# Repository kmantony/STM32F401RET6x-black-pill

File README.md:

Schematic,  PCB layout, PDF export of schematic, PCB layout/render images, BOM with estimated component cost, Short design description, ERC and DRC "Results"  are all in the result folder.

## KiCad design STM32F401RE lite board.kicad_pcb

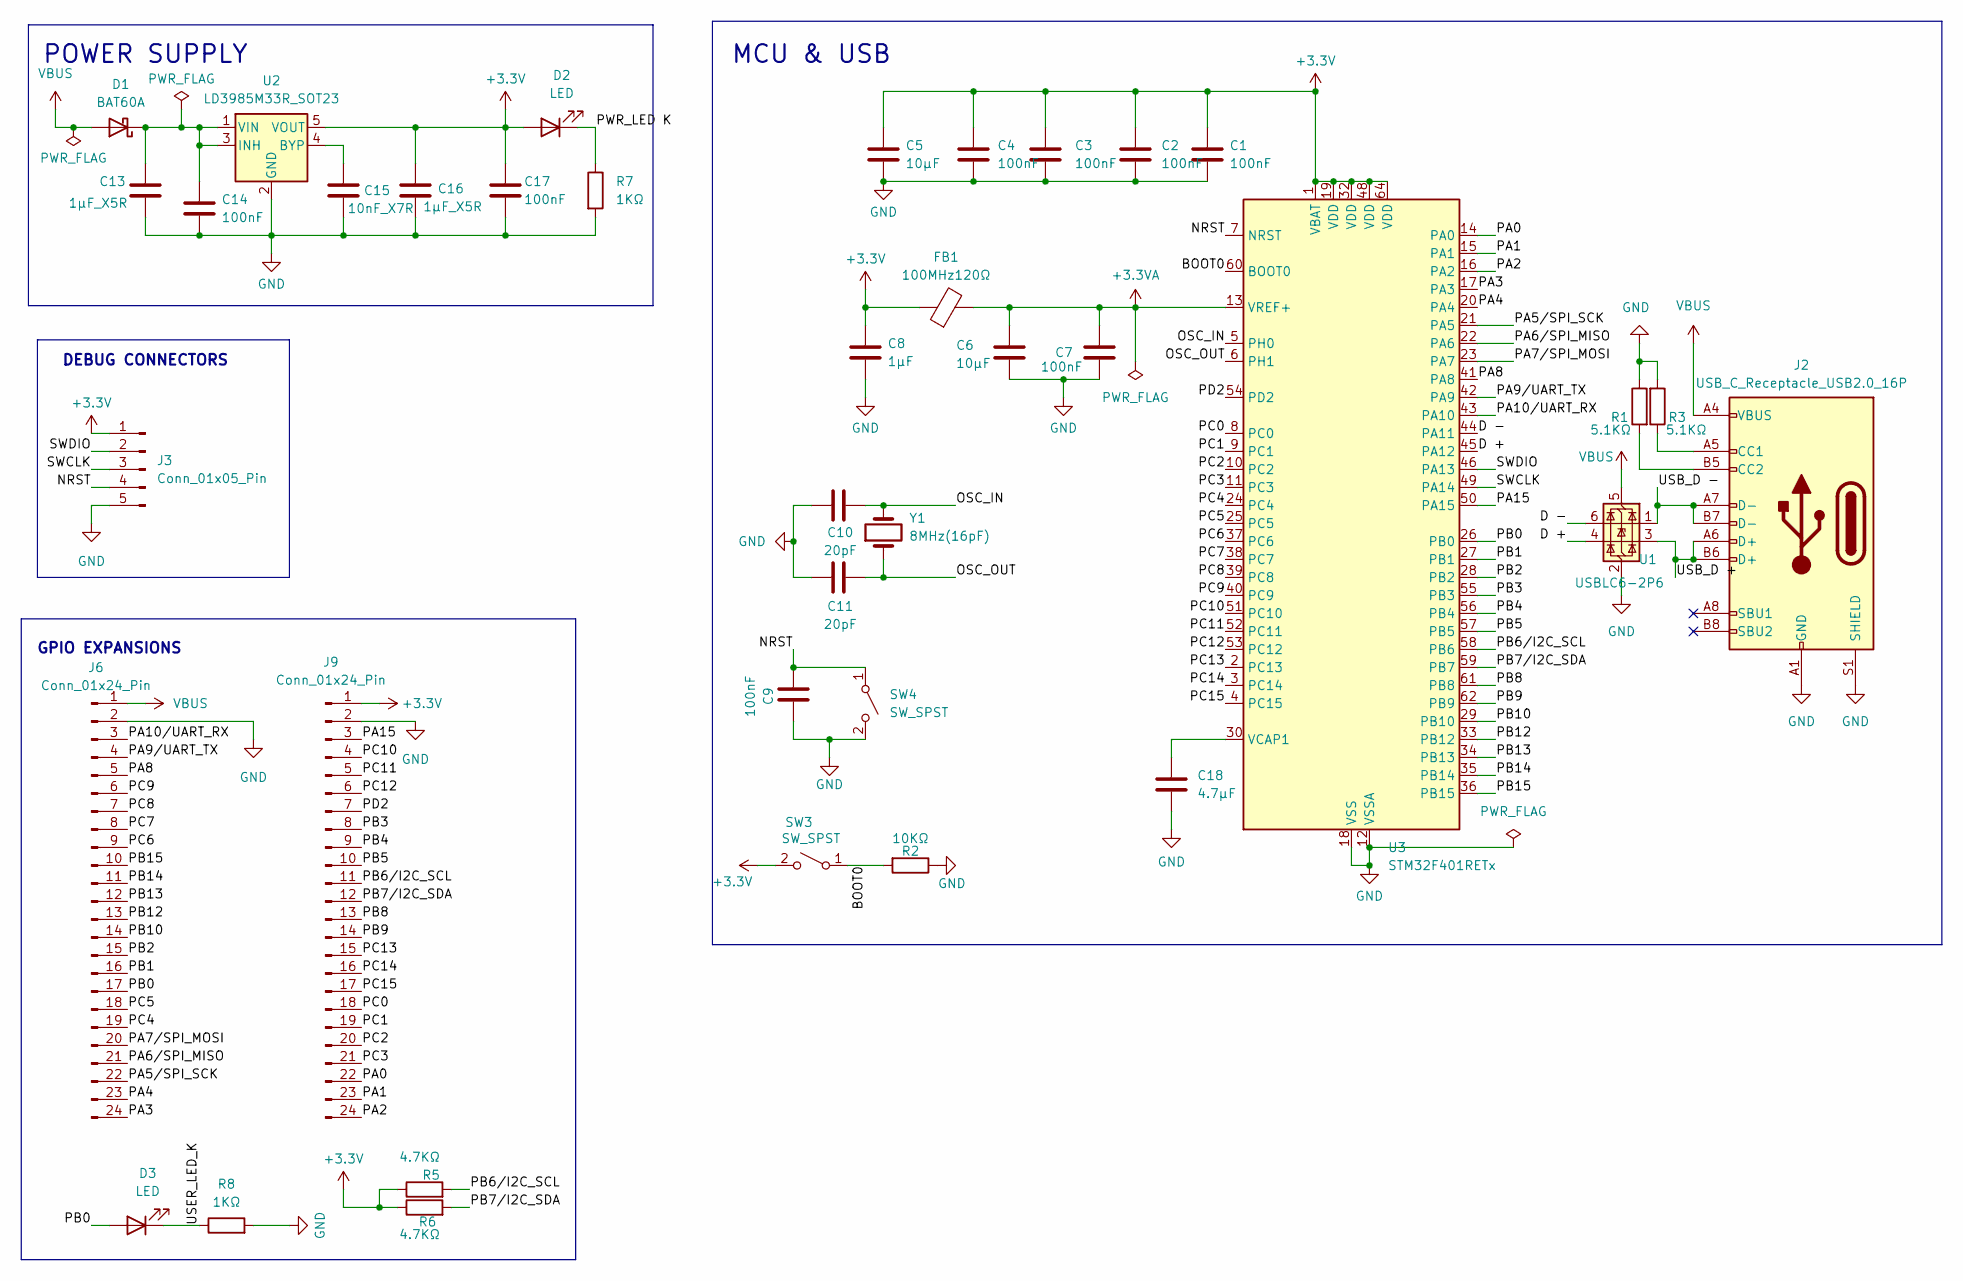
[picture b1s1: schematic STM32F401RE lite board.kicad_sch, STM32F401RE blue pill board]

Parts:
C1, C2, C3, C4, C7, C17: 100nF; C_0402_1005Metric
C5, C6: 10µF; C_0805_2012Metric
C8: 1µF; C_0402_1005Metric
C9, C14: 100nF; C_0603_1608Metric
C10, C11: 20pF; C_0402_1005Metric
C13, C16: 1µF_X5R; C_0402_1005Metric
C15: 10nF_X7R; C_0402_1005Metric
C18: 4.7µF; C_0805_2012Metric
D1: BAT60A; D_SOD-323
D2, D3: LED; LED_0603_1608Metric
FB1: 100MHz120Ω; L_0603_1608Metric
J2: USB_C_Receptacle_USB2.0_16P; USB_C_Receptacle_HRO_TYPE-C-31-M-12
J3: Conn_01x05_Pin; PinHeader_1x05_P2.54mm_Vertical
J6, J9: Conn_01x24_Pin; PinHeader_1x24_P2.54mm_Vertical
R1, R3: 5.1KΩ; R_0402_1005Metric
R2: 10KΩ; R_0402_1005Metric
R5, R6: 4.7KΩ; R_0402_1005Metric
R7, R8: 1KΩ; R_0402_1005Metric
SW3, SW4: SW_SPST; SW_SPST_TL3342
U1: USBLC6-2P6; SOT-666
U2: LD3985M33R_SOT23; SOT-23-5
U3: STM32F401RETx; LQFP-64_10x10mm_P0.5mm
Y1: 8MHz(16pF); Crystal_HC49-4H_Vertical

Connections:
+3.3V: C1.1, C2.1, C3.1, C4.1, C5.1, C8.1, C16.1, C17.1, D2.2 (A), FB1.1, J3.1, J9.1, R5.1, R6.1, SW3.2 (B), U2.5 (VOUT), U3.1 (VBAT), U3.19 (VDD), U3.32 (VDD), U3.48 (VDD), U3.64 (VDD)
+3.3VA: C6.1, C7.1, FB1.2, U3.13 (VREF+)
/BOOT0: R2.2, SW3.1 (A), U3.60 (BOOT0)
/D +: U1.4 (I/O2), U3.45 (PA12)
/D -: U1.6 (I/O1), U3.44 (PA11)
/NRST: C9.2, J3.4, SW4.1 (A), U3.7 (NRST)
/OSC_IN: C10.2, U3.5 (PH0), Y1.2
/OSC_OUT: C11.2, U3.6 (PH1), Y1.1
/PA0: J9.22, U3.14 (PA0)
/PA1: J9.23, U3.15 (PA1)
/PA2: J9.24, U3.16 (PA2)
/PA3: J6.24, U3.17 (PA3)
/PA4: J6.23, U3.20 (PA4)
/PA5/SPI_SCK: J6.22, U3.21 (PA5)
/PA6/SPI_MISO: J6.21, U3.22 (PA6)
/PA7/SPI_MOSI: J6.20, U3.23 (PA7)
/PA8: J6.5, U3.41 (PA8)
/PA9/UART_TX: J6.4, U3.42 (PA9)
/PA10/UART_RX: J6.3, U3.43 (PA10)
/PA15: J9.3, U3.50 (PA15)
/PB0: D3.2 (A), J6.17, U3.26 (PB0)
/PB1: J6.16, U3.27 (PB1)
/PB2: J6.15, U3.28 (PB2)
/PB3: J9.8, U3.55 (PB3)
/PB4: J9.9, U3.56 (PB4)
/PB5: J9.10, U3.57 (PB5)
/PB6/I2C_SCL: J9.11, R5.2, U3.58 (PB6)
/PB7/I2C_SDA: J9.12, R6.2, U3.59 (PB7)
/PB8: J9.13, U3.61 (PB8)
/PB9: J9.14, U3.62 (PB9)
/PB10: J6.14, U3.29 (PB10)
/PB12: J6.13, U3.33 (PB12)
/PB13: J6.12, U3.34 (PB13)
/PB14: J6.11, U3.35 (PB14)
/PB15: J6.10, U3.36 (PB15)
/PC0: J9.18, U3.8 (PC0)
/PC1: J9.19, U3.9 (PC1)
/PC2: J9.20, U3.10 (PC2)
/PC3: J9.21, U3.11 (PC3)
/PC4: J6.19, U3.24 (PC4)
/PC5: J6.18, U3.25 (PC5)
/PC6: J6.9, U3.37 (PC6)
/PC7: J6.8, U3.38 (PC7)
/PC8: J6.7, U3.39 (PC8)
/PC9: J6.6, U3.40 (PC9)
/PC10: J9.4, U3.51 (PC10)
/PC11: J9.5, U3.52 (PC11)
/PC12: J9.6, U3.53 (PC12)
/PC13: J9.15, U3.2 (PC13)
/PC14: J9.16, U3.3 (PC14)
/PC15: J9.17, U3.4 (PC15)
/PD2: J9.7, U3.54 (PD2)
/PWR_LED K: D2.1 (K), R7.1
/SWCLK: J3.3, U3.49 (PA14)
/SWDIO: J3.2, U3.46 (PA13)
/USB_D +: J2.A6 (D+), J2.B6 (D+), U1.3 (I/O2)
/USB_D -: J2.A7 (D-), J2.B7 (D-), U1.1 (I/O1)
/USER_LED_K: D3.1 (K), R8.1
GND: C1.2, C2.2, C3.2, C4.2, C5.2, C6.2, C7.2, C8.2, C9.1, C10.1, C11.1, C13.2, C14.2, C15.2, C16.2, C17.2, C18.2, J2.A1 (GND), J2.A12 (GND), J2.B1 (GND), J2.B12 (GND), J2.S1 (SHIELD), J3.5, J6.2, J9.2, R1.1, R2.1, R3.2, R7.2, R8.2, SW4.2 (B), U1.2 (GND), U2.2 (GND), U3.12 (VSSA), U3.18 (VSS), U3.31 (VSS), U3.47 (VSS), U3.63 (VSS)
unnamed: C13.1, C14.1, D1.1 (K), U2.1 (VIN), U2.3 (INH)
unnamed: J2.A5 (CC1), R3.1
unnamed: J2.B5 (CC2), R1.2
unnamed: C15.1, U2.4 (BYP)
unnamed: C18.1, U3.30 (VCAP1)
VBUS: D1.2 (A), J2.A4 (VBUS), J2.A9 (VBUS), J2.B4 (VBUS), J2.B9 (VBUS), J6.1, U1.5 (VBUS)

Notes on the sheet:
DEBUG CONNECTORS
POWER SUPPLY
GPIO EXPANSIONS
MCU & USB

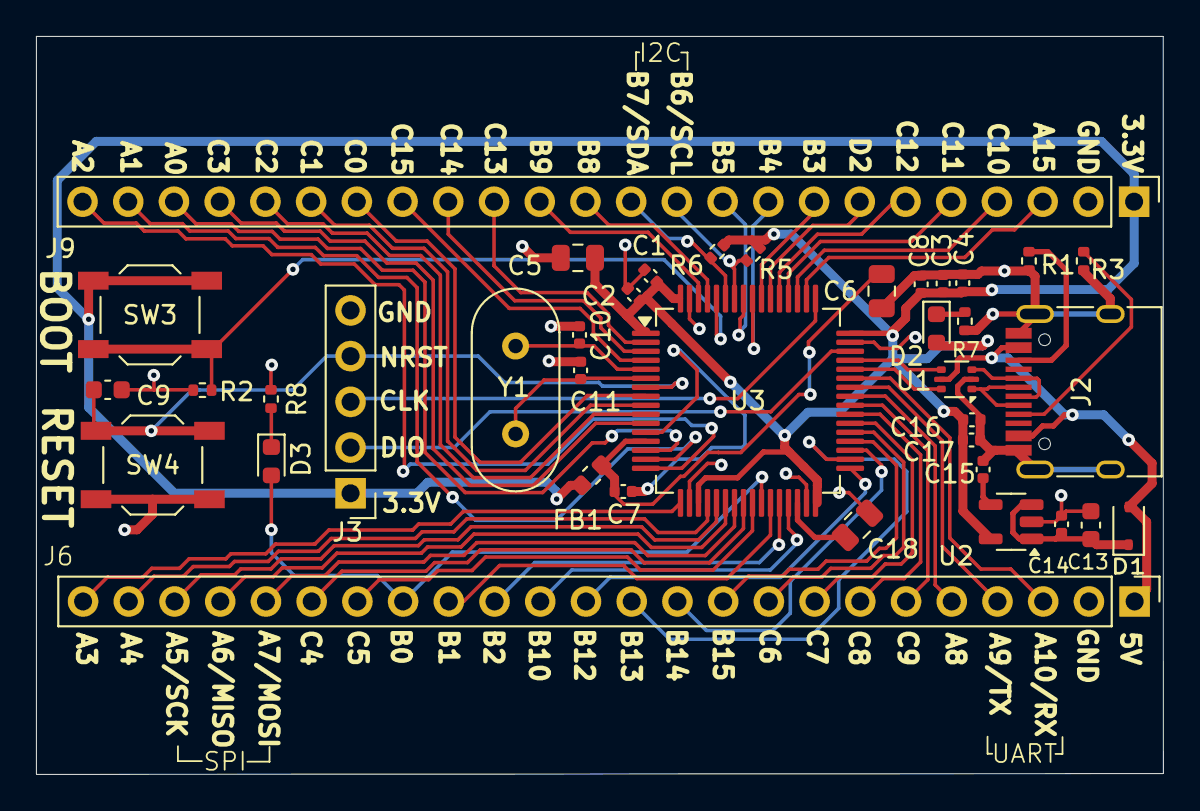
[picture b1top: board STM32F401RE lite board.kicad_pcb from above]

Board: 2 copper layers, 62.6 x 41.0 mm, 38 parts (0 on the bottom side), 65 nets.

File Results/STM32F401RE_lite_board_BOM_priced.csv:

Reference,Qty,Value,DNP,Exclude from BOM,Exclude from Board,Footprint,Datasheet,Unit Price (INR),Total Price (INR),Price Basis
"C1,C2,C3,C4,C7,C17",6,100nF,,,,Capacitor_SMD:C_0402_1005Metric,~,0.24,1.44,Indicative generic 0402 MLCC
"C5,C6",2,10µF,,,,Capacitor_SMD:C_0805_2012Metric,~,0.78,1.56,Indicative generic 10uF 0805 MLCC
C8,1,1µF,,,,Capacitor_SMD:C_0402_1005Metric,~,0.4,0.4,Indicative generic 1uF 0402 MLCC
"C9,C14",2,100nF,,,,Capacitor_SMD:C_0603_1608Metric,~,0.24,0.48,Indicative generic 0603 100nF MLCC
"C10,C11",2,20pF,,,,Capacitor_SMD:C_0402_1005Metric,~,1.86,3.72,Indicative 20pF 0402 C0G/NP0
"C13,C16",2,1µF_X5R,,,,Capacitor_SMD:C_0402_1005Metric,~,0.4,0.8,Indicative generic 1uF X5R 0402 MLCC
C15,1,10nF_X7R,,,,Capacitor_SMD:C_0402_1005Metric,~,0.4,0.4,Indicative generic 10nF X7R 0402 MLCC
C18,1,4.7µF,,,,Capacitor_SMD:C_0805_2012Metric,~,1.5,1.5,Indicative generic 4.7uF 0805 MLCC
D1,1,BAT60A,,,,Diode_SMD:D_SOD-323,https://www.infineon.com/dgdl/Infineon-BAT60ASERIES-DS-v01_0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,19.11,19.11,DigiKey India indicative price
"D2,D3",2,LED,,,,LED_SMD:LED_0603_1608Metric,~,0.5,1.0,Indicative generic 0603 LED
FB1,1,100MHz120Ω,,,,Inductor_SMD:L_0603_1608Metric,~,0.8,0.8,Indicative generic 0603 ferrite bead
J2,1,USB_C_Receptacle_USB2.0_16P,,,,Connector_USB:USB_C_Receptacle_HRO_TYPE-C-31-M-12,https://www.usb.org/sites/default/files/documents/usb_type-c.zip,15.0,15.0,Indicative TYPE-C-31-M-12 equivalent
J3,1,Conn_01x05_Pin,,,,Connector_PinHeader_2.54mm:PinHeader_1x05_P2.54mm_Vertical,~,5.0,5.0,Indicative generic 1x05 2.54mm header
"J6,J9",2,Conn_01x24_Pin,,,,Connector_PinHeader_2.54mm:PinHeader_1x24_P2.54mm_Vertical,~,8.0,16.0,Indicative generic 1x24 2.54mm header
"R1,R3",2,5.1KΩ,,,,Resistor_SMD:R_0402_1005Metric,~,0.18,0.36,KTRON India indicative 0402 resistor
R2,1,10KΩ,,,,Resistor_SMD:R_0402_1005Metric,~,0.18,0.18,Indicative generic 0402 resistor
"R5,R6",2,4.7KΩ,,,,Resistor_SMD:R_0402_1005Metric,~,0.18,0.36,Indicative generic 0402 resistor
"R7,R8",2,1KΩ,,,,Resistor_SMD:R_0402_1005Metric,~,0.18,0.36,Indicative generic 0402 resistor
"SW3,SW4",2,SW_SPST,,,,Button_Switch_SMD:SW_SPST_TL3342,~,56.37,112.74,DigiKey India TL3342 indicative price
U1,1,USBLC6-2P6,,,,Package_TO_SOT_SMD:SOT-666,https://www.st.com/resource/en/datasheet/usblc6-2.pdf,62.11,62.11,DigiKey India USBLC6-2P6 indicative price
U2,1,LD3985M33R_SOT23,,,,Package_TO_SOT_SMD:SOT-23-5,http://www.st.com/internet/com/TECHNICAL_RESOURCES/TECHNICAL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,74.53,74.53,DigiKey India LD3985M33R indicative price
U3,1,STM32F401RETx,,,,Package_QFP:LQFP-64_10x10mm_P0.5mm,https://www.st.com/resource/en/datasheet/stm32f401re.pdf,729.6,729.6,Mouser India STM32F401RET6 indicative price
Y1,1,8MHz(16pF),,,,Crystal:Crystal_HC49-4H_Vertical,~,5.0,5.0,Indicative generic 8MHz HC49 crystal
